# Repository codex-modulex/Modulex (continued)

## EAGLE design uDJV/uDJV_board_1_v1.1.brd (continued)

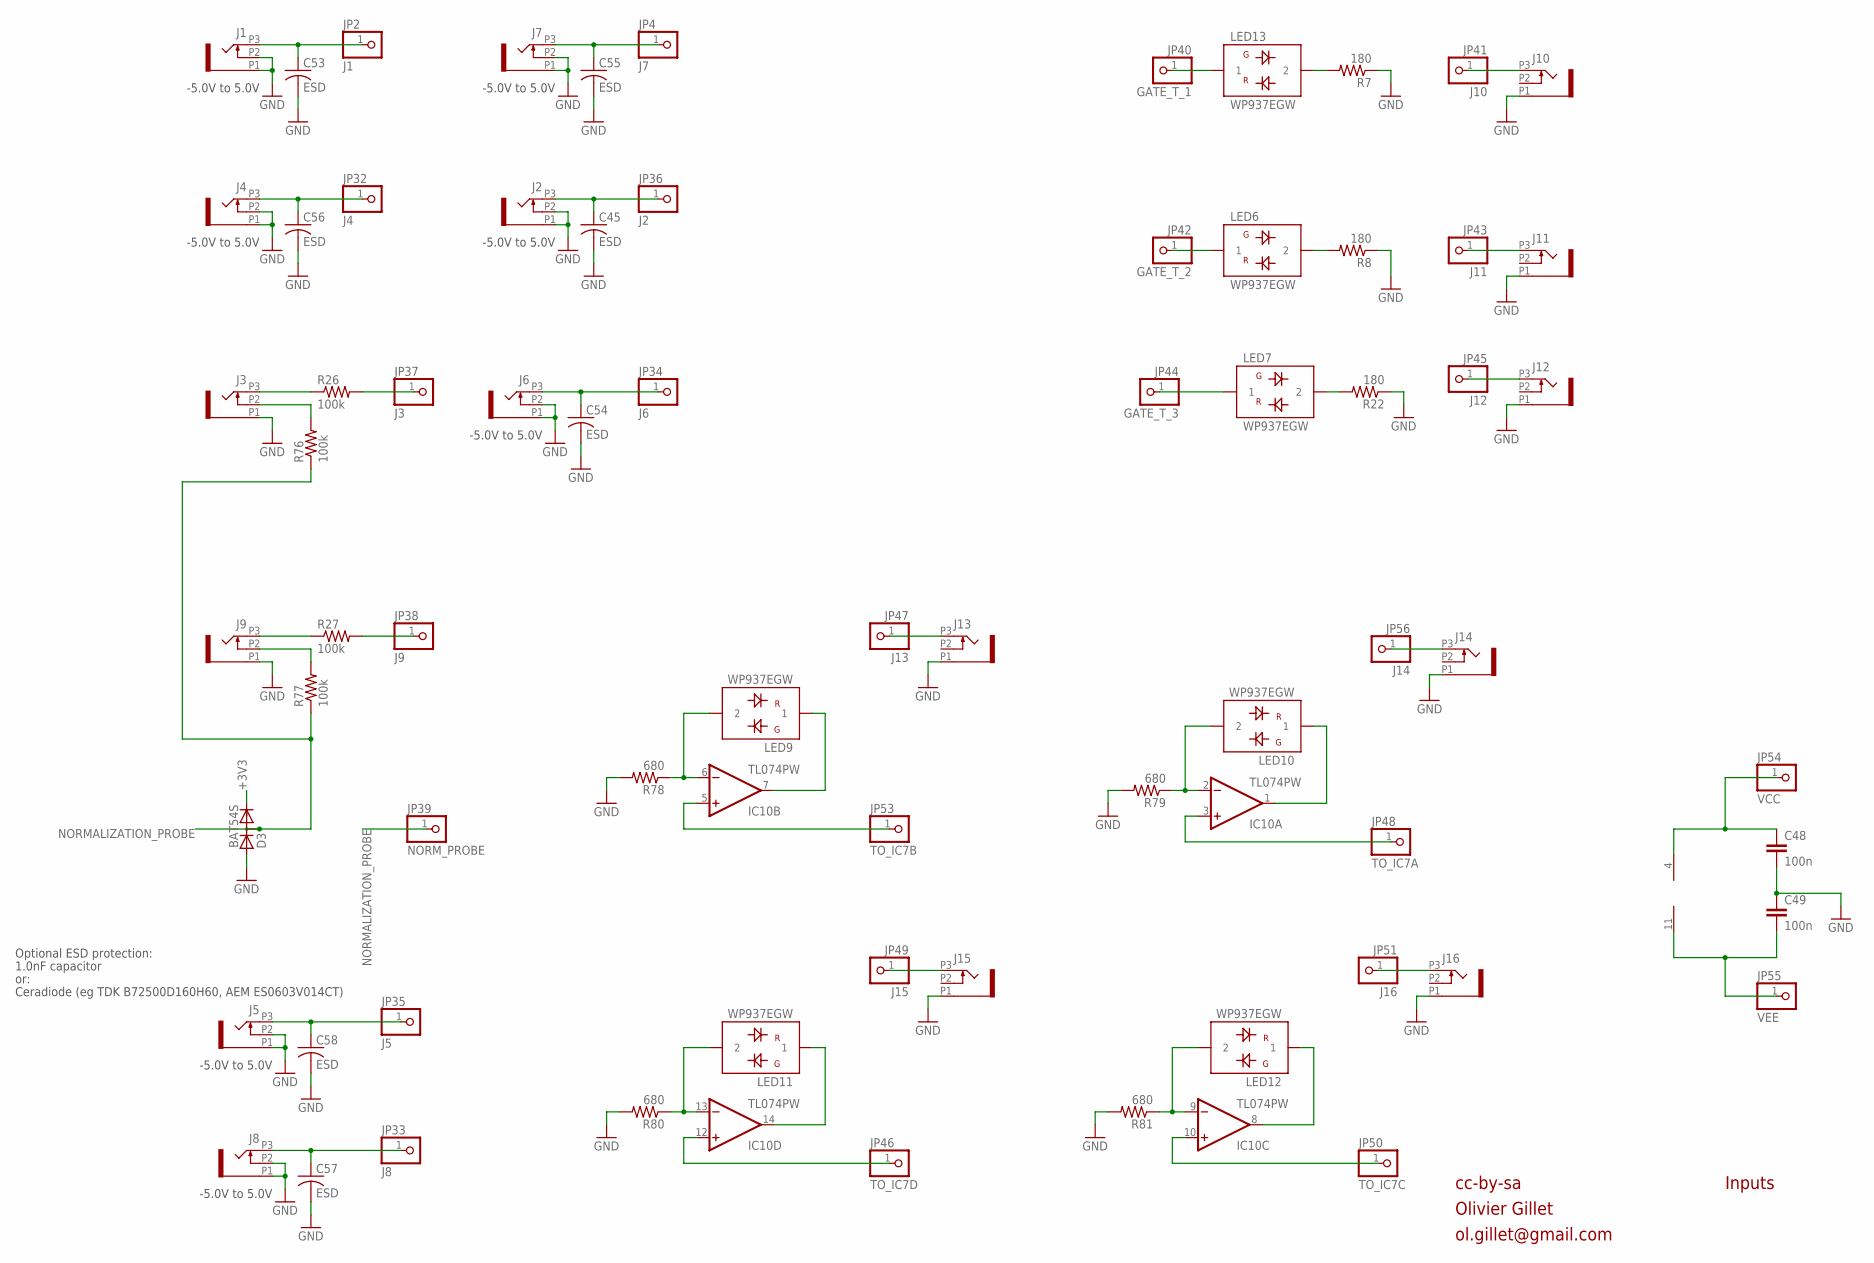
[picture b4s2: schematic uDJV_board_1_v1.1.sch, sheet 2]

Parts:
C45, C53, C54, C55, C56, C57, C58: ESD; C0603
C48, C49: 100n; PARTS_AMAN_RESISTOR_0603
D3: BAT54S; SOT23
IC10: TL074PW; TSSOP14_065
J1, J2, J3, J4, J5, J6, J7, J8, J9, J10, J11, J12, J13, J14, J15, J16: PJ301_THONKICONN6; WQP_PJ_301M6
JP2: J1; PARTS_AMAN_1X01
JP4: J7; PARTS_AMAN_1X01
JP32: J4; PARTS_AMAN_1X01
JP33: J8; PARTS_AMAN_1X01
JP34: J6; PARTS_AMAN_1X01
JP35: J5; PARTS_AMAN_1X01
JP36: J2; PARTS_AMAN_1X01
JP37: J3; PARTS_AMAN_1X01
JP38: J9; PARTS_AMAN_1X01
JP39: NORM_PROBE; PARTS_AMAN_1X01
JP40: GATE_T_1; PARTS_AMAN_1X01
JP41: J10; PARTS_AMAN_1X01
JP42: GATE_T_2; PARTS_AMAN_1X01
JP43: J11; PARTS_AMAN_1X01
JP44: GATE_T_3; PARTS_AMAN_1X01
JP45: J12; PARTS_AMAN_1X01
JP46: TO_IC7D; PARTS_AMAN_1X01
JP47: J13; PARTS_AMAN_1X01
JP48: TO_IC7A; PARTS_AMAN_1X01
JP49: J15; PARTS_AMAN_1X01
JP50: TO_IC7C; PARTS_AMAN_1X01
JP51: J16; PARTS_AMAN_1X01
JP53: TO_IC7B; PARTS_AMAN_1X01
JP54: VCC; PARTS_AMAN_1X01
JP55: VEE; PARTS_AMAN_1X01
JP56: J14; PARTS_AMAN_1X01
LED6, LED7, LED9, LED10, LED11, LED12, LED13: WP937EGW; LED3MM
R7, R8, R22: 180; PARTS_AMAN_RESISTOR_0603
R26, R27, R76, R77: 100k; PARTS_AMAN_RESISTOR_0603
R78, R79, R80, R81: 680; PARTS_AMAN_RESISTOR_0603

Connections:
+3V3: D3.2 (C)
GATE_T_2: JP42.1, LED6.1
GND: C45.2, C48.2, C49.1, C53.2, C54.2, C55.2, C56.2, C57.2, C58.2, D3.1 (A), J1.P1 (1), J1.P2 (2), J2.P1 (1), J2.P2 (2), J3.P1 (1), J4.P1 (1), J4.P2 (2), J5.P1 (1), J5.P2 (2), J6.P1 (1), J6.P2 (2), J7.P1 (1), J7.P2 (2), J8.P1 (1), J8.P2 (2), J9.P1 (1), J10.P1 (1), J11.P1 (1), J12.P1 (1), J13.P1 (1), J14.P1 (1), J15.P1 (1), J16.P1 (1), R7.1, R8.1, R22.1, R78.2, R79.2, R80.2, R81.2; also elsewhere on the board
MORPH_IN: C53.1, J1.P3 (3), JP2.1
MORPH_IN1: C55.1, J7.P3 (3), JP4.1
MORPH_IN3: C56.1, J4.P3 (3), JP32.1
MORPH_IN4: C57.1, J8.P3 (3), JP33.1
MORPH_IN5: C54.1, J6.P3 (3), JP34.1
MORPH_IN6: C58.1, J5.P3 (3), JP35.1
MORPH_IN7: C45.1, J2.P3 (3), JP36.1
unnamed: C49.2, IC10.11 (V-), JP55.1
unnamed: JP37.1, R26.2
unnamed: JP38.1, R27.2
unnamed: JP40.1, LED13.1
unnamed: J10.P3 (3), JP41.1
unnamed: J12.P3 (3), JP45.1
unnamed: LED13.2, R7.2
unnamed: J11.P3 (3), JP43.1
unnamed: J16.P3 (3), JP51.1
unnamed: LED6.2, R8.2
unnamed: LED7.2, R22.2
unnamed: JP44.1, LED7.1
unnamed: C48.1, IC10.4 (V+), JP54.1
unnamed: J9.P3 (3), R27.1
unnamed: IC10.5 (+IN), JP53.1
unnamed: J9.P2 (2), R77.2
unnamed: J3.P2 (2), R76.2
unnamed: J15.P3 (3), JP49.1
unnamed: J13.P3 (3), JP47.1
unnamed: J3.P3 (3), R26.1
unnamed: J14.P3 (3), JP56.1
unnamed: IC10.6 (-IN), LED9.2, R78.1
unnamed: IC10.7 (OUT), LED9.1
unnamed: IC10.3 (+IN), JP48.1
unnamed: IC10.2 (-IN), LED10.2, R79.1
unnamed: IC10.1 (OUT), LED10.1
unnamed: IC10.12 (+IN), JP46.1
unnamed: IC10.13 (-IN), LED11.2, R80.1
unnamed: IC10.14 (OUT), LED11.1
unnamed: IC10.10 (+IN), JP50.1
unnamed: IC10.9 (-IN), LED12.2, R81.1
unnamed: IC10.8 (OUT), LED12.1
NORMALIZATION_PROBE: D3.3 (AC), JP39.1, R76.1, R77.1

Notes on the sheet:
cc-by-sa
Olivier Gillet
ol.gillet@gmail.com
Inputs
-5.0V to 5.0V
Optional ESD protection:
1.0nF capacitor
or:
Ceradiode (eg TDK B72500D160H60, AEM ES0603V014CT)

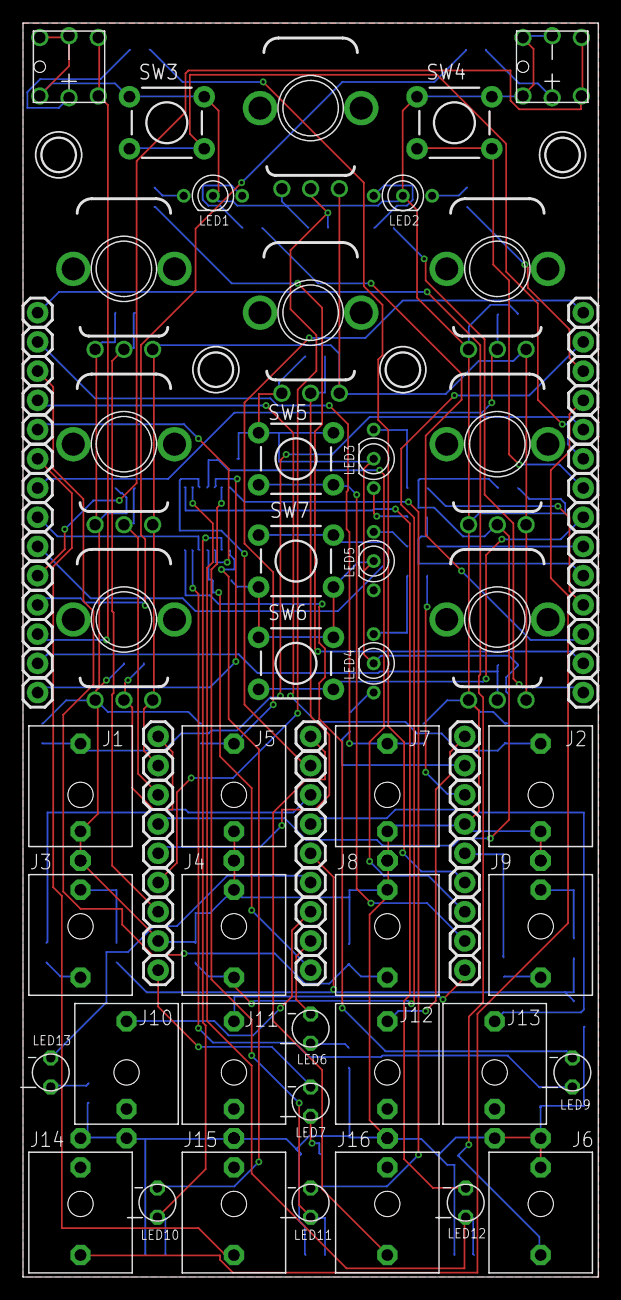
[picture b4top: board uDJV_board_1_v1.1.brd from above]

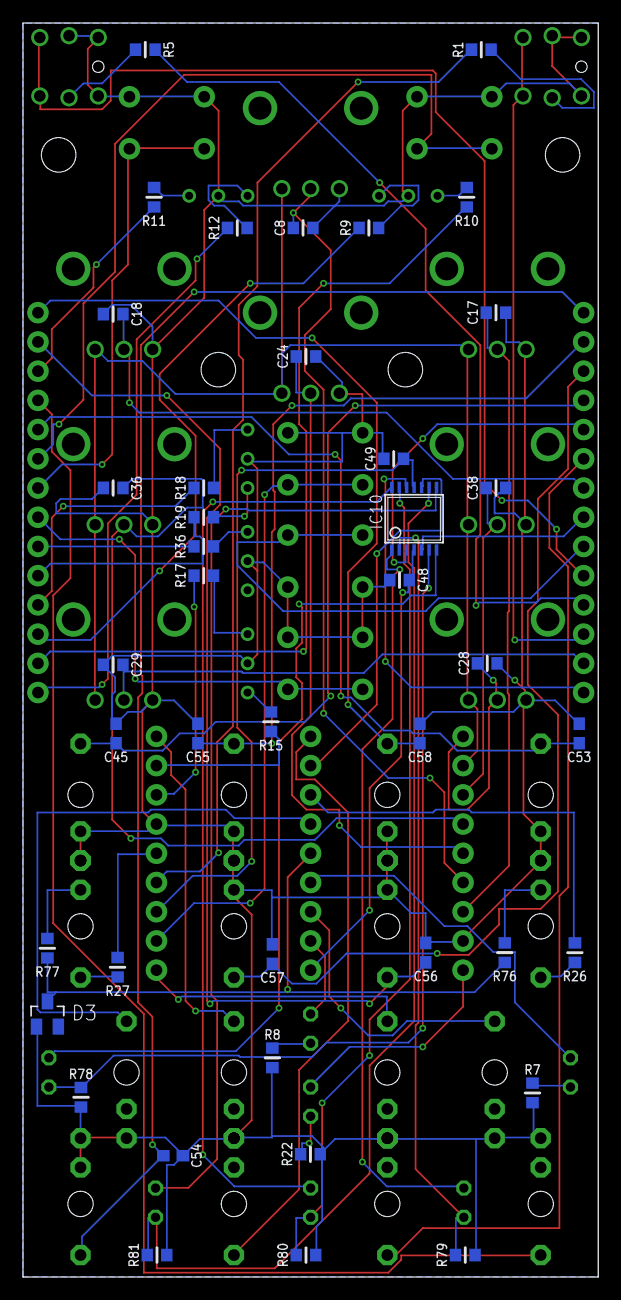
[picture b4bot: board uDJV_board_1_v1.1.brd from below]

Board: 2 copper layers, 50.0 x 109.0 mm, 143 parts (41 on the bottom side), 80 nets.

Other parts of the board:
H3, H4: MOUNT-HOLE3.0TINY; 3,0TINY

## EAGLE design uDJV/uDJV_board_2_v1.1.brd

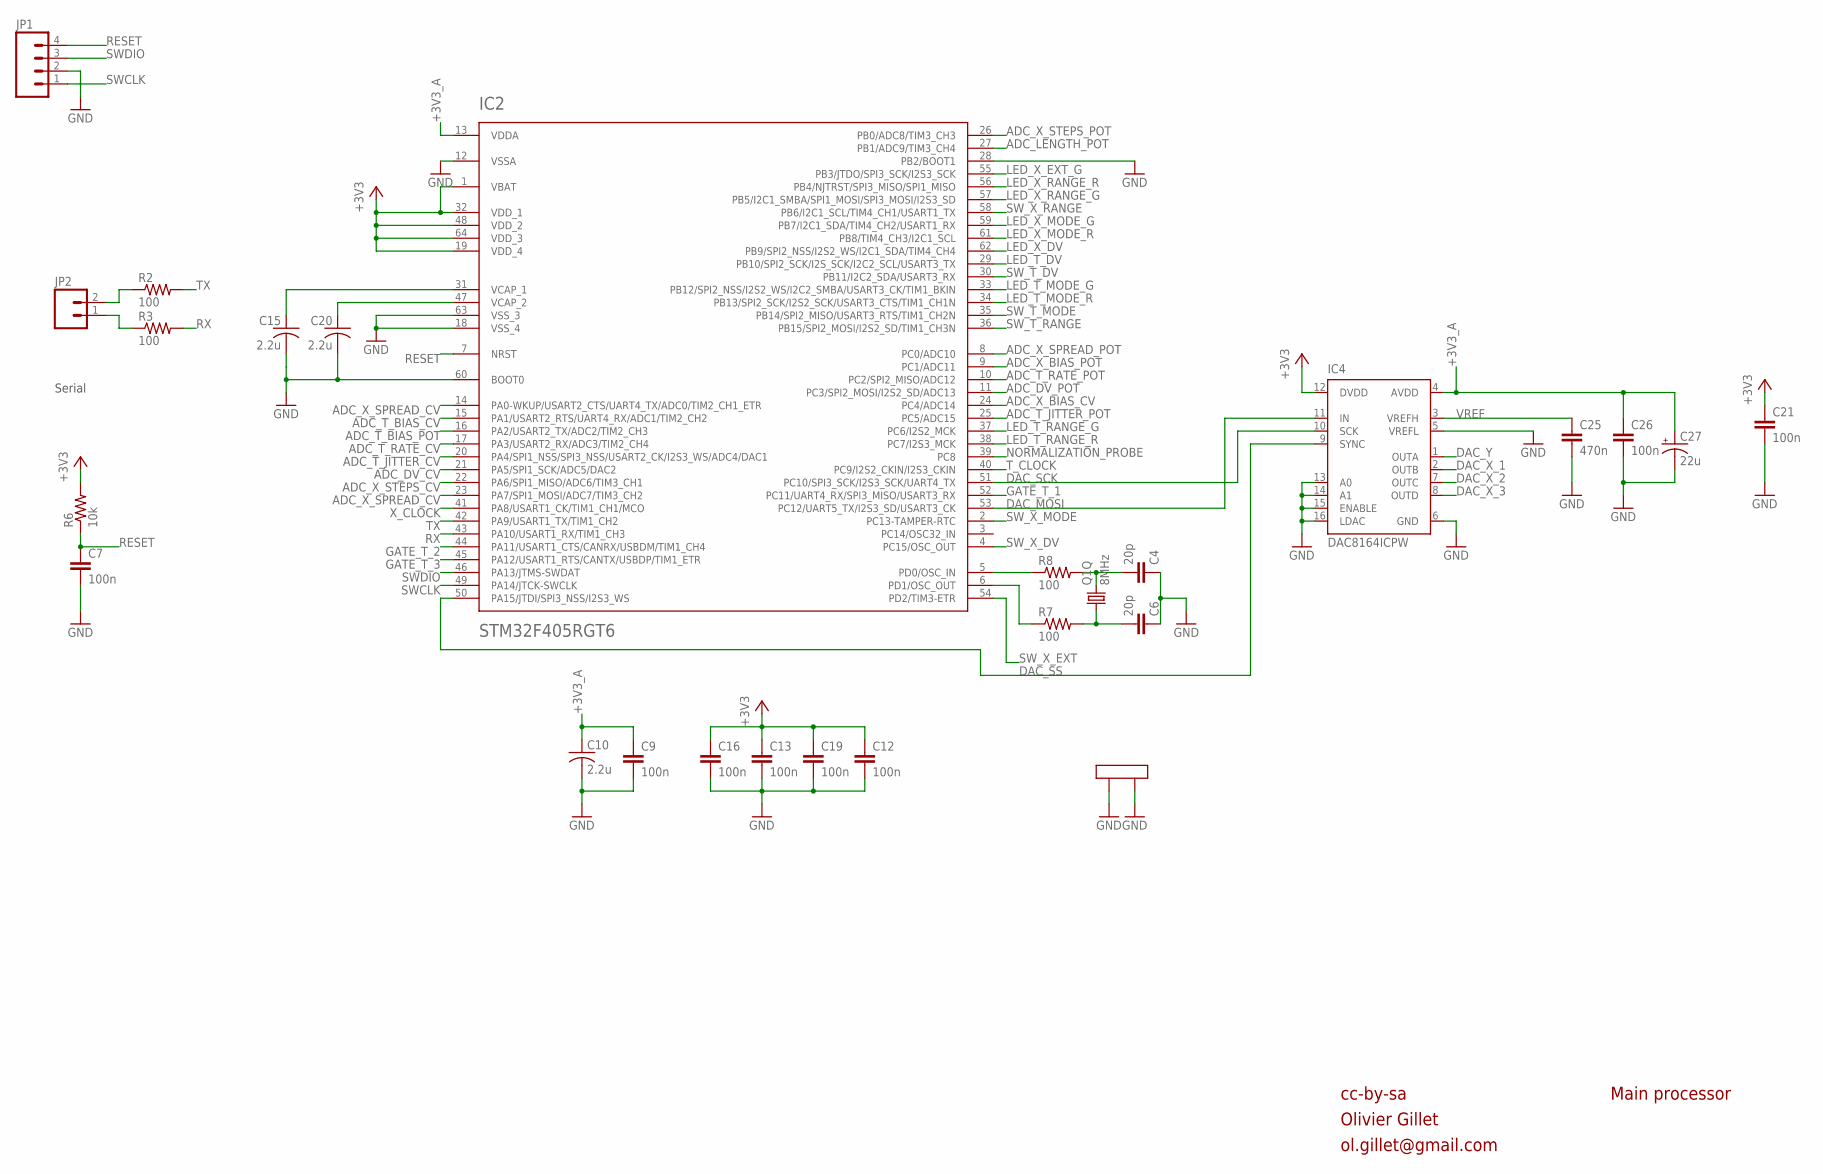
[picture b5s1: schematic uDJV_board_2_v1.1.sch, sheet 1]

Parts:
C4, C6: 20p; PARTS_AMAN_RESISTOR_0603
C7, C9, C12, C13, C16, C19, C21, C26: 100n; PARTS_AMAN_RESISTOR_0603
C10, C15, C20: 2.2u; C0805
C25: 470n; PARTS_AMAN_RESISTOR_0603
C27: 22u; PANASONIC_C
IC2: STM32F405RGT6; TQFP-10X10-64
IC4: DAC8164ICPW; SOP65P640X110-16N
JP1: M04PTH; 1X04
JP2: M02PTH; 1X02
Q1: 8MHz; CTS406
R2, R3, R7, R8: 100; PARTS_AMAN_RESISTOR_0603
R6: 10k; PARTS_AMAN_RESISTOR_0603

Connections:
+3V3: C12.1, C13.1, C16.1, C19.1, C21.1, IC2.1 (VBAT), IC2.19 (VDD_4), IC2.32 (VDD_1), IC2.48 (VDD_2), IC2.64 (VDD_3), IC4.12 (DVDD), R6.2; also elsewhere on the board
+3V3_A: C9.1, C10.1, C26.1, C27.+, IC2.13 (VDDA), IC4.4 (AVDD); also elsewhere on the board
ADC_DV_CV: IC2.21 (PA5/SPI1_SCK/ADC5/DAC2); also elsewhere on the board
ADC_DV_POT: IC2.11 (PC3/SPI2_MOSI/I2S2_SD/ADC13); also elsewhere on the board
ADC_LENGTH_POT: IC2.27 (PB1/ADC9/TIM3_CH4); also elsewhere on the board
ADC_T_BIAS_CV: IC2.15 (PA1/USART2_RTS/UART4_RX/ADC1/TIM2_CH2); also elsewhere on the board
ADC_T_BIAS_POT: IC2.16 (PA2/USART2_TX/ADC2/TIM2_CH3); also elsewhere on the board
ADC_T_JITTER_CV: IC2.20 (PA4/SPI1_NSS/SPI3_NSS/USART2_CK/I2S3_WS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); also elsewhere on the board
ADC_T_JITTER_POT: IC2.25 (PC5/ADC15); also elsewhere on the board
ADC_T_RATE_CV: IC2.17 (PA3/USART2_RX/ADC3/TIM2_CH4); also elsewhere on the board
ADC_T_RATE_POT: IC2.10 (PC2/SPI2_MISO/ADC12); also elsewhere on the board
ADC_X_BIAS_CV: IC2.24 (PC4/ADC14); also elsewhere on the board
ADC_X_BIAS_POT: IC2.9 (PC1/ADC11); also elsewhere on the board
ADC_X_SPREAD_CV: IC2.14 (PA0-WKUP/USART2_CTS/UART4_TX/ADC0/TIM2_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), IC2.23 (PA7/SPI1_MOSI/ADC7/TIM3_CH2); also elsewhere on the board
ADC_X_SPREAD_POT: IC2.8 (PC0/ADC10); also elsewhere on the board
ADC_X_STEPS_CV: IC2.22 (PA6/SPI1_MISO/ADC6/TIM3_CH1); also elsewhere on the board
ADC_X_STEPS_POT: IC2.26 (PB0/ADC8/TIM3_CH3); also elsewhere on the board
DAC_MOSI: IC2.53 (PC12/UART5_TX/I2S3_SD/USART3_CK), IC4.11 (IN)
DAC_SCK: IC2.51 (PC10/SPI3_SCK/I2S3_SCK/UART4_TX), IC4.10 (SCK)
DAC_SS: IC2.50 (PA15/JTDI/SPI3_NSS/I2S3_WS), IC4.9 (SYNC)
DAC_X_1: IC4.2 (OUTB); also elsewhere on the board
DAC_X_2: IC4.7 (OUTC); also elsewhere on the board
DAC_X_3: IC4.8 (OUTD); also elsewhere on the board
DAC_Y: IC4.1 (OUTA); also elsewhere on the board
GATE_T_1: IC2.52 (PC11/UART4_RX/SPI3_MISO/USART3_RX); also elsewhere on the board
GATE_T_2: IC2.44 (PA11/USART1_CTS/CANRX/USBDM/TIM1_CH4); also elsewhere on the board
GATE_T_3: IC2.45 (PA12/USART1_RTS/CANTX/USBDP/TIM1_ETR); also elsewhere on the board
GND: C4.1, C6.1, C7.2, C9.2, C10.2, C12.2, C13.2, C15.2, C16.2, C19.2, C20.2, C21.2, C25.2, C26.2, C27.-, IC2.12 (VSSA), IC2.18 (VSS_4), IC2.28 (PB2/BOOT1), IC2.60 (BOOT0), IC2.63 (VSS_3), IC4.5 (VREFL), IC4.6 (GND), IC4.13 (A0), IC4.14 (A1), IC4.15 (ENABLE), IC4.16 (LDAC), JP1.2, Q1.2 (LID1), Q1.4 (LID2); also elsewhere on the board
LED_T_DV: IC2.29 (PB10/SPI2_SCK/I2S_SCK/I2C2_SCL/USART3_TX); also elsewhere on the board
LED_T_MODE_G: IC2.33 (PB12/SPI2_NSS/I2S2_WS/I2C2_SMBA/USART3_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); also elsewhere on the board
LED_T_MODE_R: IC2.34 (PB13/SPI2_SCK/I2S2_SCK/USART3_CTS/TIM1_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); also elsewhere on the board
LED_T_RANGE_G: IC2.37 (PC6/I2S2_MCK); also elsewhere on the board
LED_T_RANGE_R: IC2.38 (PC7/I2S3_MCK); also elsewhere on the board
LED_X_DV: IC2.62 (PB9/SPI2_NSS/I2S2_WS/I2C1_SDA/TIM4_CH4); also elsewhere on the board
LED_X_EXT_G: IC2.55 (PB3/JTDO/SPI3_SCK/I2S3_SCK); also elsewhere on the board
LED_X_MODE_G: IC2.59 (PB7/I2C1_SDA/TIM4_CH2/USART1_RX); also elsewhere on the board
LED_X_MODE_R: IC2.61 (PB8/TIM4_CH3/I2C1_SCL); also elsewhere on the board
LED_X_RANGE_G: IC2.57 (PB5/I2C1_SMBA/SPI1_MOSI/SPI3_MOSI/I2S3_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); also elsewhere on the board
LED_X_RANGE_R: IC2.56 (PB4/NJTRST/SPI3_MISO/SPI1_MISO); also elsewhere on the board
unnamed: IC2.6 (PD1/OSC_OUT), R7.1
unnamed: IC2.5 (PD0/OSC_IN), R8.1
unnamed: C20.1, IC2.47 (VCAP_2)
unnamed: C15.1, IC2.31 (VCAP_1)
unnamed: JP2.2, R2.1
unnamed: JP2.1, R3.1
unnamed: C4.2, Q1.3 (2), R8.2
unnamed: C6.2, Q1.1, R7.2
NORMALIZATION_PROBE: IC2.39 (PC8); also elsewhere on the board
RESET: C7.1, IC2.7 (NRST), JP1.4, R6.1
RX: IC2.43 (PA10/USART1_RX/TIM1_CH3), R3.2
SWCLK: IC2.49 (PA14/JTCK-SWCLK), JP1.1
SWDIO: IC2.46 (PA13/JTMS-SWDAT), JP1.3
SW_T_DV: IC2.30 (PB11/I2C2_SDA/USART3_RX); also elsewhere on the board
SW_T_MODE: IC2.35 (PB14/SPI2_MISO/USART3_RTS/TIM1_CH2N); also elsewhere on the board
SW_T_RANGE: IC2.36 (PB15/SPI2_MOSI/I2S2_SD/TIM1_CH3N); also elsewhere on the board
SW_X_DV: IC2.4 (PC15/OSC_OUT); also elsewhere on the board
SW_X_EXT: IC2.54 (PD2/TIM3-ETR); also elsewhere on the board
SW_X_MODE: IC2.2 (PC13-TAMPER-RTC); also elsewhere on the board
SW_X_RANGE: IC2.58 (PB6/I2C1_SCL/TIM4_CH1/USART1_TX); also elsewhere on the board
TX: IC2.42 (PA9/USART1_TX/TIM1_CH2), R2.2
T_CLOCK: IC2.40 (PC9/I2S2_CKIN/I2S3_CKIN); also elsewhere on the board
VREF: C25.1, IC4.3 (VREFH); also elsewhere on the board
X_CLOCK: IC2.41 (PA8/USART1_CK/TIM1_CH1/MCO); also elsewhere on the board

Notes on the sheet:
cc-by-sa
Olivier Gillet
ol.gillet@gmail.com
Main processor
Serial

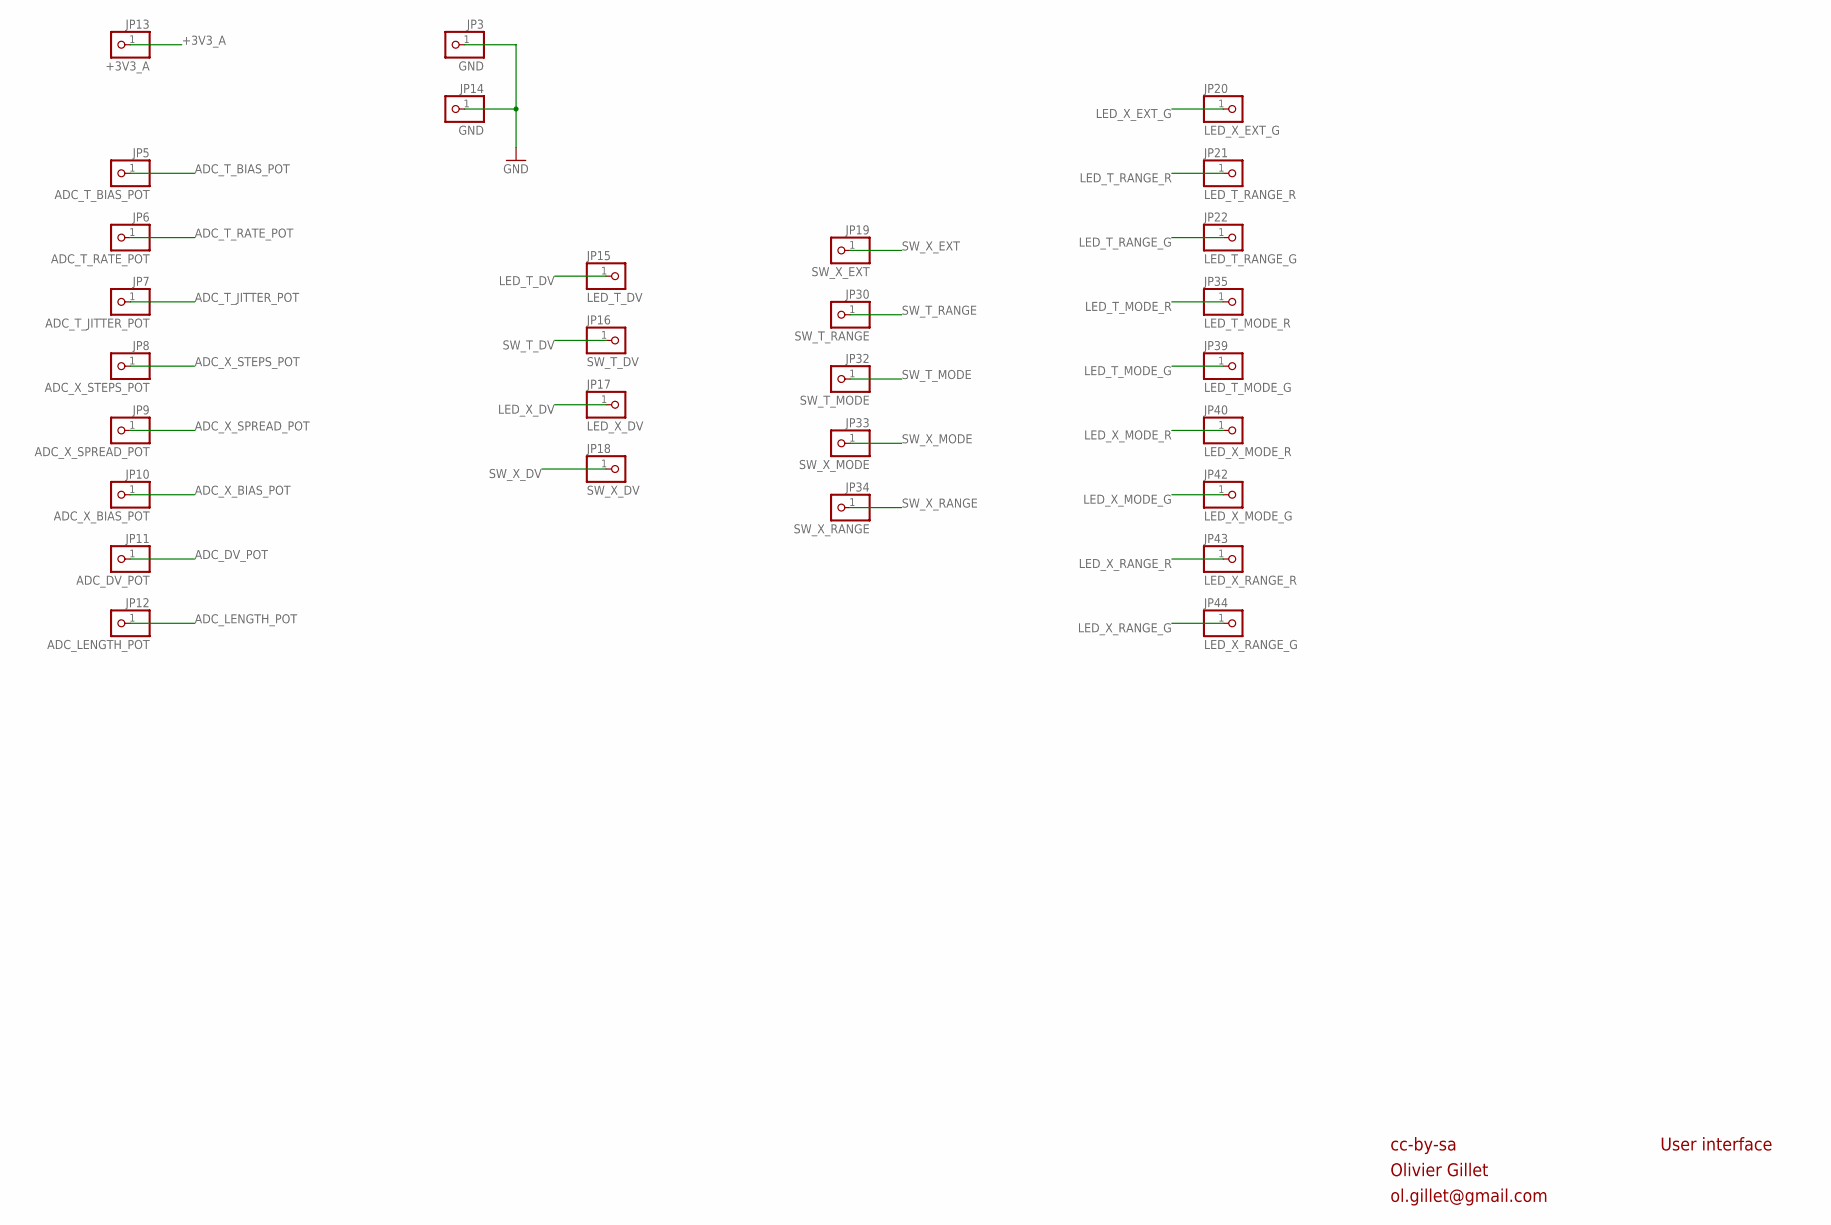
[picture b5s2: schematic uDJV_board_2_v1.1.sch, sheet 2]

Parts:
JP3, JP14: GND; PARTS_AMAN_1X01
JP5: ADC_T_BIAS_POT; PARTS_AMAN_1X01
JP6: ADC_T_RATE_POT; PARTS_AMAN_1X01
JP7: ADC_T_JITTER_POT; PARTS_AMAN_1X01
JP8: ADC_X_STEPS_POT; PARTS_AMAN_1X01
JP9: ADC_X_SPREAD_POT; PARTS_AMAN_1X01
JP10: ADC_X_BIAS_POT; PARTS_AMAN_1X01
JP11: ADC_DV_POT; PARTS_AMAN_1X01
JP12: ADC_LENGTH_POT; PARTS_AMAN_1X01
JP13: +3V3_A; PARTS_AMAN_1X01
JP15: LED_T_DV; PARTS_AMAN_1X01
JP16: SW_T_DV; PARTS_AMAN_1X01
JP17: LED_X_DV; PARTS_AMAN_1X01
JP18: SW_X_DV; PARTS_AMAN_1X01
JP19: SW_X_EXT; PARTS_AMAN_1X01
JP20: LED_X_EXT_G; PARTS_AMAN_1X01
JP21: LED_T_RANGE_R; PARTS_AMAN_1X01
JP22: LED_T_RANGE_G; PARTS_AMAN_1X01
JP30: SW_T_RANGE; PARTS_AMAN_1X01
JP32: SW_T_MODE; PARTS_AMAN_1X01
JP33: SW_X_MODE; PARTS_AMAN_1X01
JP34: SW_X_RANGE; PARTS_AMAN_1X01
JP35: LED_T_MODE_R; PARTS_AMAN_1X01
JP39: LED_T_MODE_G; PARTS_AMAN_1X01
JP40: LED_X_MODE_R; PARTS_AMAN_1X01
JP42: LED_X_MODE_G; PARTS_AMAN_1X01
JP43: LED_X_RANGE_R; PARTS_AMAN_1X01
JP44: LED_X_RANGE_G; PARTS_AMAN_1X01

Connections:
+3V3_A: JP13.1; also elsewhere on the board
ADC_DV_POT: JP11.1; also elsewhere on the board
ADC_LENGTH_POT: JP12.1; also elsewhere on the board
ADC_T_BIAS_POT: JP5.1; also elsewhere on the board
ADC_T_JITTER_POT: JP7.1; also elsewhere on the board
ADC_T_RATE_POT: JP6.1; also elsewhere on the board
ADC_X_BIAS_POT: JP10.1; also elsewhere on the board
ADC_X_SPREAD_POT: JP9.1; also elsewhere on the board
ADC_X_STEPS_POT: JP8.1; also elsewhere on the board
GND: JP3.1, JP14.1; also elsewhere on the board
LED_T_DV: JP15.1; also elsewhere on the board
LED_T_MODE_G: JP39.1; also elsewhere on the board
LED_T_MODE_R: JP35.1; also elsewhere on the board
LED_T_RANGE_G: JP22.1; also elsewhere on the board
LED_T_RANGE_R: JP21.1; also elsewhere on the board
LED_X_DV: JP17.1; also elsewhere on the board
LED_X_EXT_G: JP20.1; also elsewhere on the board
LED_X_MODE_G: JP42.1; also elsewhere on the board
LED_X_MODE_R: JP40.1; also elsewhere on the board
LED_X_RANGE_G: JP44.1; also elsewhere on the board
LED_X_RANGE_R: JP43.1; also elsewhere on the board
SW_T_DV: JP16.1; also elsewhere on the board
SW_T_MODE: JP32.1; also elsewhere on the board
SW_T_RANGE: JP30.1; also elsewhere on the board
SW_X_DV: JP18.1; also elsewhere on the board
SW_X_EXT: JP19.1; also elsewhere on the board
SW_X_MODE: JP33.1; also elsewhere on the board
SW_X_RANGE: JP34.1; also elsewhere on the board

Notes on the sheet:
cc-by-sa
Olivier Gillet
ol.gillet@gmail.com
User interface

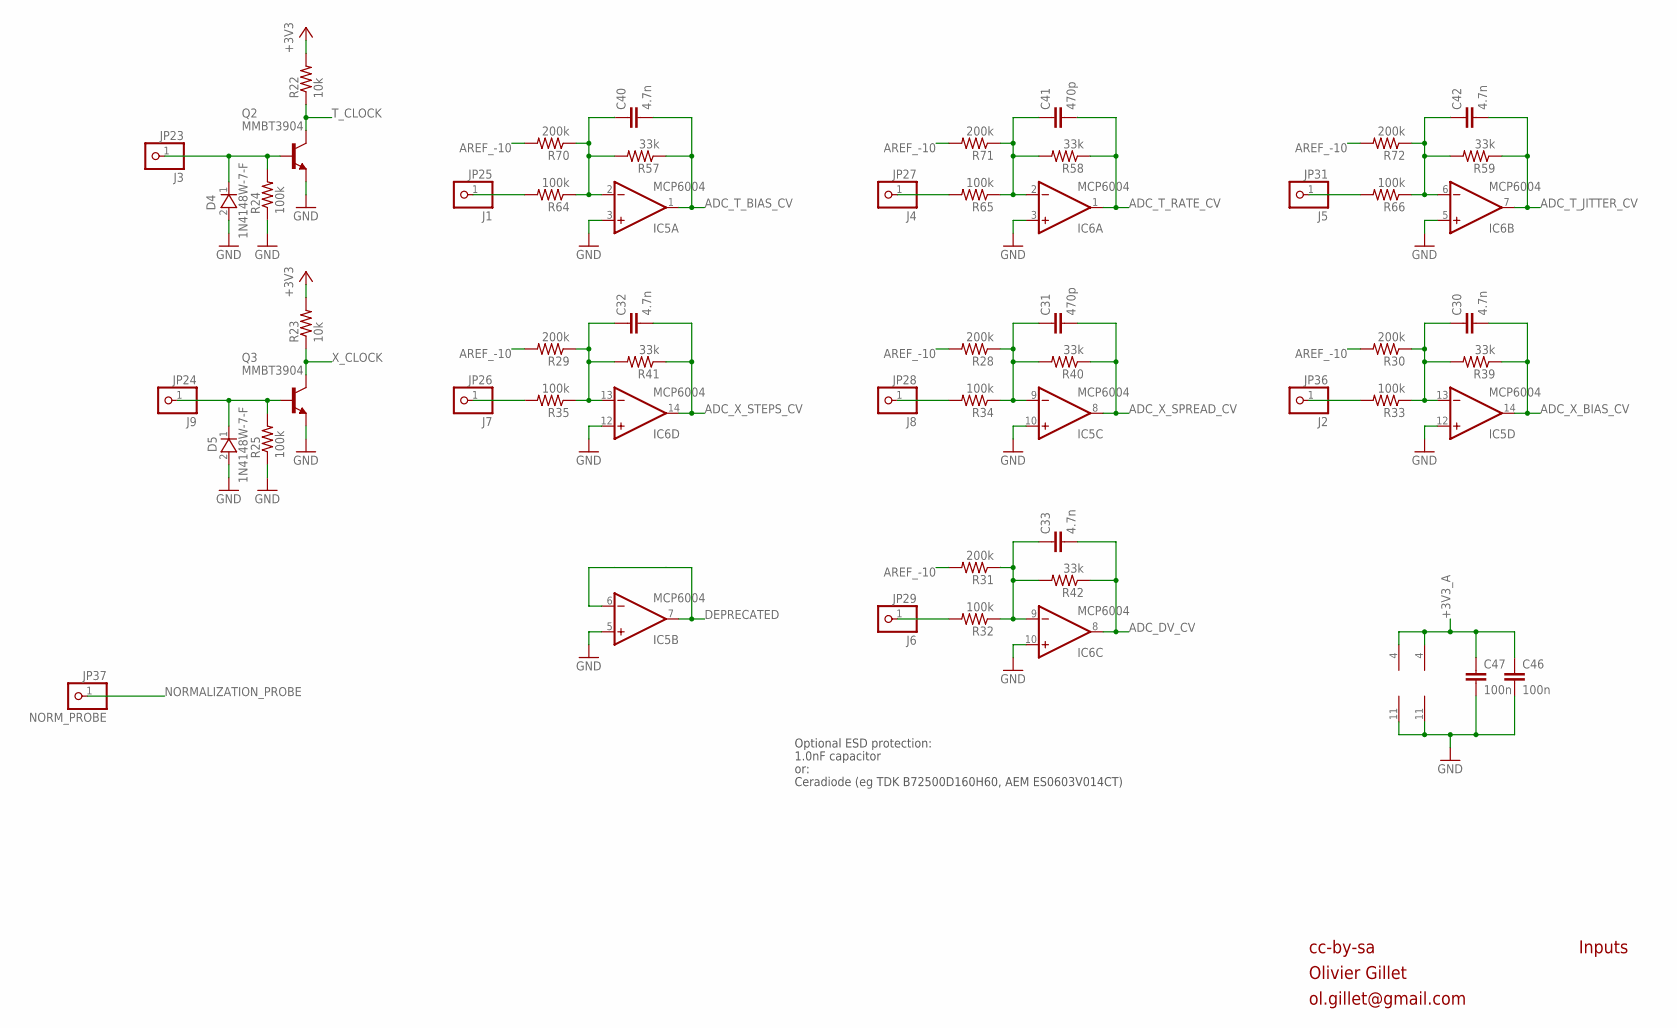
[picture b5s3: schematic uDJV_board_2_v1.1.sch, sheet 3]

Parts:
C30, C32, C33, C40, C42: 4.7n; PARTS_AMAN_RESISTOR_0603
C31, C41: 470p; PARTS_AMAN_RESISTOR_0603
C46, C47: 100n; PARTS_AMAN_RESISTOR_0603
D4, D5: 1N4148W-7-F; SOD3716X115N
IC5, IC6: MCP6004; TSSOP14_065
JP23: J3; PARTS_AMAN_1X01
JP24: J9; PARTS_AMAN_1X01
JP25: J1; PARTS_AMAN_1X01
JP26: J7; PARTS_AMAN_1X01
JP27: J4; PARTS_AMAN_1X01
JP28: J8; PARTS_AMAN_1X01
JP29: J6; PARTS_AMAN_1X01
JP31: J5; PARTS_AMAN_1X01
JP36: J2; PARTS_AMAN_1X01
JP37: NORM_PROBE; PARTS_AMAN_1X01
Q2, Q3: MMBT3904; SOT23-BEC
R22, R23: 10k; PARTS_AMAN_RESISTOR_0603
R24, R25, R32, R33, R34, R35, R64, R65, R66: 100k; PARTS_AMAN_RESISTOR_0603
R28, R29, R30, R31, R70, R71, R72: 200k; PARTS_AMAN_RESISTOR_0603
R39, R40, R41, R42, R57, R58, R59: 33k; PARTS_AMAN_RESISTOR_0603

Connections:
+3V3: R22.2, R23.2; also elsewhere on the board
+3V3_A: C46.1, C47.1, IC5.4 (V+), IC6.4 (V+); also elsewhere on the board
ADC_DV_CV: C33.2, IC6.8 (OUT), R42.1; also elsewhere on the board
ADC_T_BIAS_CV: C40.2, IC5.1 (OUT), R57.1; also elsewhere on the board
ADC_T_JITTER_CV: C42.2, IC6.7 (OUT), R59.1; also elsewhere on the board
ADC_T_RATE_CV: C41.2, IC6.1 (OUT), R58.1; also elsewhere on the board
ADC_X_BIAS_CV: C30.2, IC5.14 (OUT), R39.1; also elsewhere on the board
ADC_X_SPREAD_CV: C31.2, IC5.8 (OUT), R40.1; also elsewhere on the board
ADC_X_STEPS_CV: C32.2, IC6.14 (OUT), R41.1; also elsewhere on the board
AREF_-10: R28.2, R29.2, R30.2, R31.2, R70.2, R71.2, R72.2; also elsewhere on the board
DEPRECATED: IC5.6 (-IN), IC5.7 (OUT)
GND: C46.2, C47.2, D4.2 (A), D5.2 (A), IC5.3 (+IN), IC5.5 (+IN), IC5.10 (+IN), IC5.11 (V-), IC5.12 (+IN), IC6.3 (+IN), IC6.5 (+IN), IC6.10 (+IN), IC6.11 (V-), IC6.12 (+IN), Q2.E, Q3.E, R24.1, R25.1; also elsewhere on the board
MORPH_IN: JP25.1, R64.2
MORPH_IN1: JP26.1, R35.2
MORPH_IN3: JP27.1, R65.2
MORPH_IN4: JP28.1, R34.2
MORPH_IN5: JP29.1, R32.2
MORPH_IN6: JP31.1, R66.2
MORPH_IN7: JP36.1, R33.2
unnamed: C41.1, IC6.2 (-IN), R58.2, R65.1, R71.1
unnamed: C40.1, IC5.2 (-IN), R57.2, R64.1, R70.1
unnamed: C42.1, IC6.6 (-IN), R59.2, R66.1, R72.1
unnamed: C31.1, IC5.9 (-IN), R28.1, R34.1, R40.2
unnamed: C30.1, IC5.13 (-IN), R30.1, R33.1, R39.2
unnamed: C32.1, IC6.13 (-IN), R29.1, R35.1, R41.2
unnamed: C33.1, IC6.9 (-IN), R31.1, R32.1, R42.2
unnamed: D4.1 (K), JP23.1, Q2.B, R24.2
unnamed: D5.1 (K), JP24.1, Q3.B, R25.2
NORMALIZATION_PROBE: JP37.1; also elsewhere on the board
T_CLOCK: Q2.C, R22.1; also elsewhere on the board
X_CLOCK: Q3.C, R23.1; also elsewhere on the board

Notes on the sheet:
cc-by-sa
Olivier Gillet
ol.gillet@gmail.com
Inputs
Optional ESD protection:
1.0nF capacitor
or:
Ceradiode (eg TDK B72500D160H60, AEM ES0603V014CT)

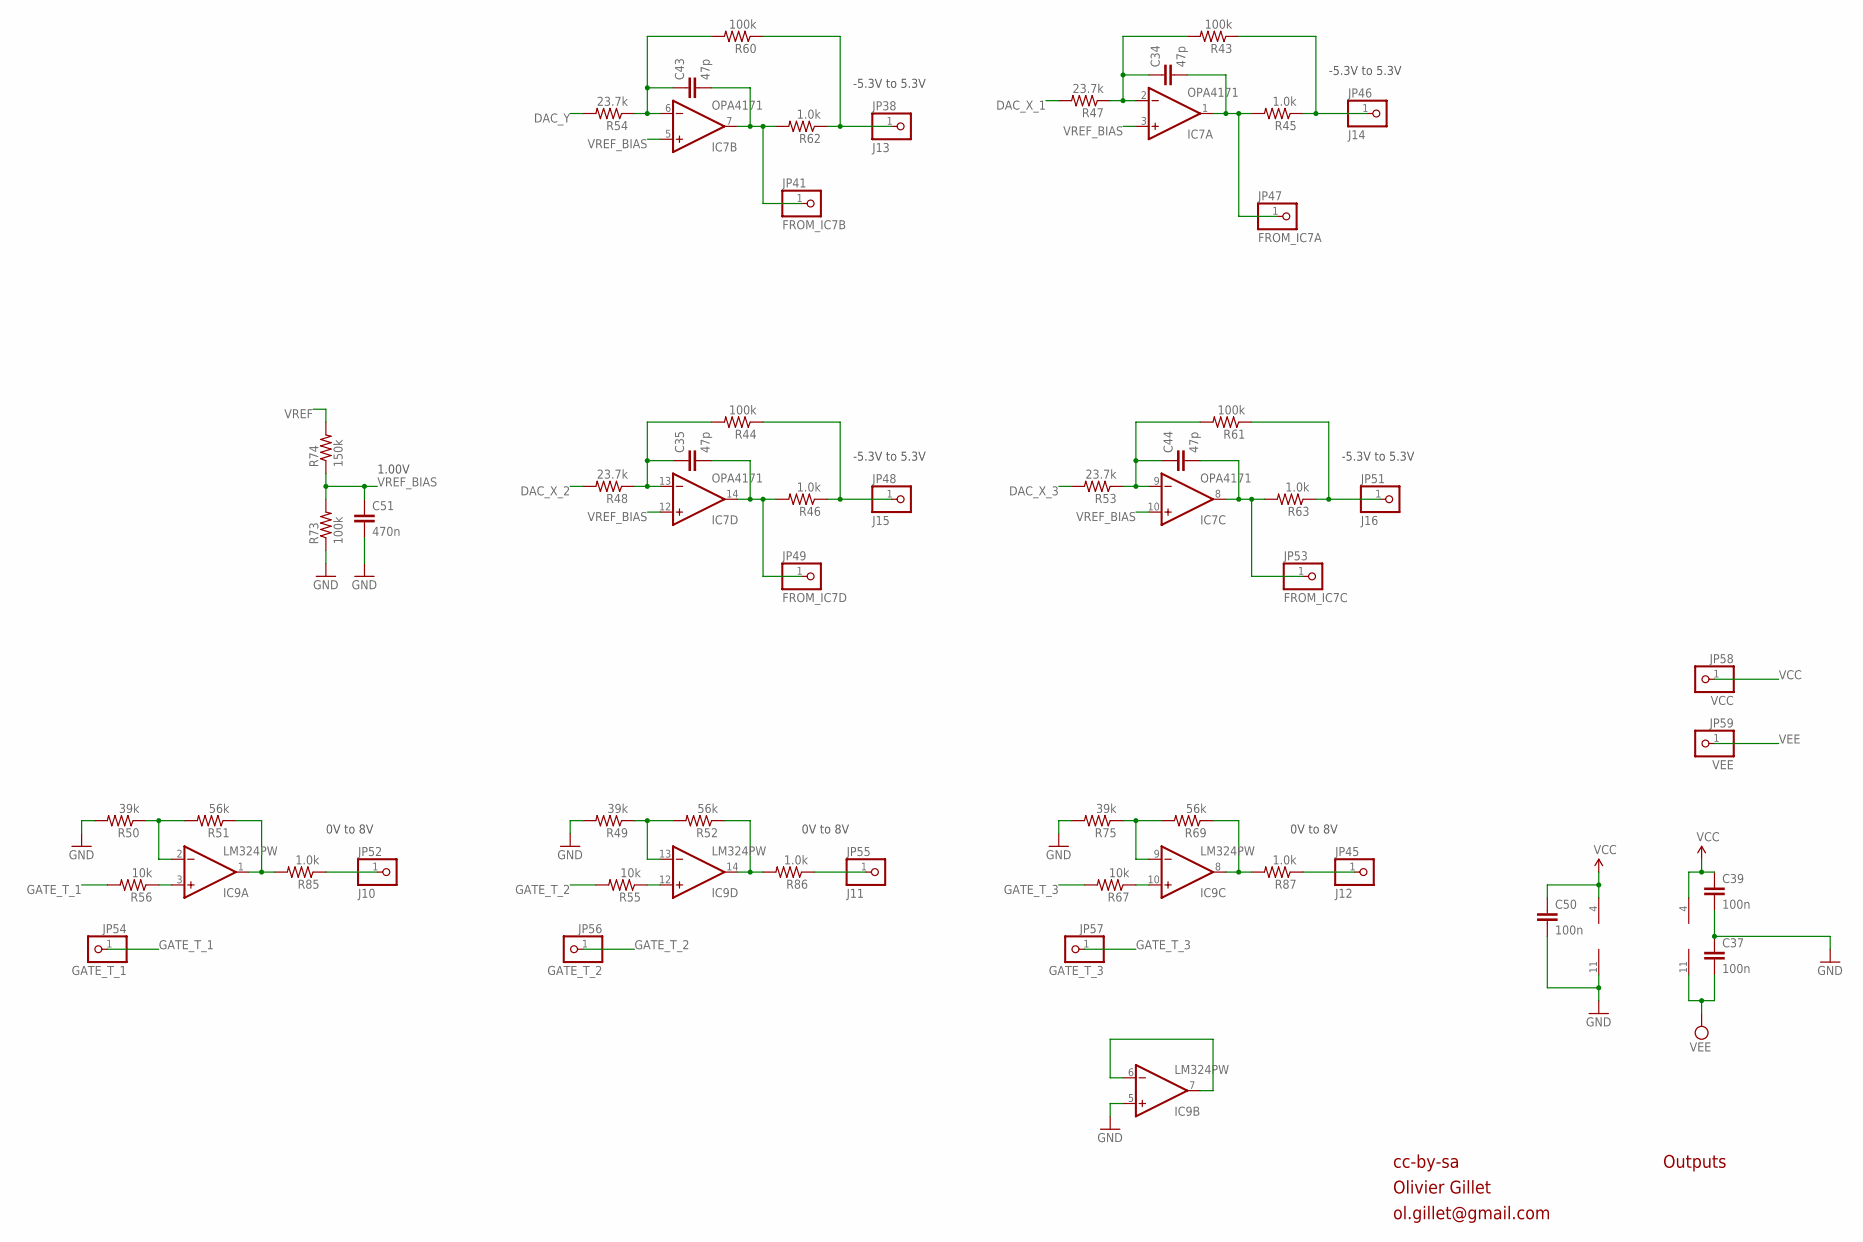
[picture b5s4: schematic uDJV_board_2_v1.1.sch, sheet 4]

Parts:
C34, C35, C43, C44: 47p; PARTS_AMAN_RESISTOR_0603
C37, C39, C50: 100n; PARTS_AMAN_RESISTOR_0603
C51: 470n; PARTS_AMAN_RESISTOR_0603
IC7: OPA4171; TSSOP14_065
IC9: LM324PW; TSSOP14_065
JP38: J13; PARTS_AMAN_1X01
JP41: FROM_IC7B; PARTS_AMAN_1X01
JP45: J12; PARTS_AMAN_1X01
JP46: J14; PARTS_AMAN_1X01
JP47: FROM_IC7A; PARTS_AMAN_1X01
JP48: J15; PARTS_AMAN_1X01
JP49: FROM_IC7D; PARTS_AMAN_1X01
JP51: J16; PARTS_AMAN_1X01
JP52: J10; PARTS_AMAN_1X01
JP53: FROM_IC7C; PARTS_AMAN_1X01
JP54: GATE_T_1; PARTS_AMAN_1X01
JP55: J11; PARTS_AMAN_1X01
JP56: GATE_T_2; PARTS_AMAN_1X01
JP57: GATE_T_3; PARTS_AMAN_1X01
JP58: VCC; PARTS_AMAN_1X01
JP59: VEE; PARTS_AMAN_1X01
R43, R44, R60, R61, R73: 100k; PARTS_AMAN_RESISTOR_0603
R45: 1.0k; PARTS_AMAN_RESISTOR_0603
R46, R62, R63, R85, R86, R87: 1.0k; R0603
R47, R48, R53, R54: 23.7k; PARTS_AMAN_RESISTOR_0603
R49, R50, R75: 39k; PARTS_AMAN_RESISTOR_0603
R51, R52, R69: 56k; PARTS_AMAN_RESISTOR_0603
R55, R56, R67: 10k; PARTS_AMAN_RESISTOR_0603
R74: 150k; PARTS_AMAN_RESISTOR_0603

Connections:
DAC_X_1: R47.2; also elsewhere on the board
DAC_X_2: R48.2; also elsewhere on the board
DAC_X_3: R53.2; also elsewhere on the board
DAC_Y: R54.2; also elsewhere on the board
GATE_T_1: JP54.1, R56.2; also elsewhere on the board
GATE_T_2: JP56.1, R55.2; also elsewhere on the board
GATE_T_3: JP57.1, R67.2; also elsewhere on the board
GND: C37.1, C39.2, C50.2, C51.2, IC9.5 (+IN), IC9.11 (V-), R49.2, R50.2, R73.1, R75.2; also elsewhere on the board
unnamed: IC9.12 (+IN), R55.1
unnamed: IC9.1 (OUT), R51.1, R85.2
unnamed: JP52.1, R85.1
unnamed: IC9.2 (-IN), R50.1, R51.2
unnamed: IC9.3 (+IN), R56.1
unnamed: IC9.6 (-IN), IC9.7 (OUT)
unnamed: IC9.14 (OUT), R52.1, R86.2
unnamed: IC9.13 (-IN), R49.1, R52.2
unnamed: IC9.10 (+IN), R67.1
unnamed: IC9.8 (OUT), R69.1, R87.2
unnamed: JP55.1, R86.1
unnamed: JP45.1, R87.1
unnamed: IC9.9 (-IN), R69.2, R75.1
unnamed: C43.2, IC7.7 (OUT), JP41.1, R62.2
unnamed: JP48.1, R44.1, R46.1
unnamed: JP38.1, R60.1, R62.1
unnamed: C35.1, IC7.13 (-IN), R44.2, R48.1
unnamed: JP51.1, R61.1, R63.1
unnamed: C44.1, IC7.9 (-IN), R53.1, R61.2
unnamed: C34.1, IC7.2 (-IN), R43.2, R47.1
unnamed: C43.1, IC7.6 (-IN), R54.1, R60.2
unnamed: JP46.1, R43.1, R45.1
unnamed: C34.2, IC7.1 (OUT), JP47.1, R45.2
unnamed: C35.2, IC7.14 (OUT), JP49.1, R46.2
unnamed: C44.2, IC7.8 (OUT), JP53.1, R63.2
VCC: C39.1, C50.1, IC7.4 (V+), IC9.4 (V+), JP58.1; also elsewhere on the board
VEE: C37.2, IC7.11 (V-), JP59.1; also elsewhere on the board
VREF: R74.2; also elsewhere on the board
VREF_BIAS: C51.1, IC7.3 (+IN), IC7.5 (+IN), IC7.10 (+IN), IC7.12 (+IN), R73.2, R74.1

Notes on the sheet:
-5.3V to 5.3V
0V to 8V
cc-by-sa
Olivier Gillet
ol.gillet@gmail.com
Outputs
1.00V
